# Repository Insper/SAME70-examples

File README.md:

Example projects to the SAME70-XPLD microchip development kit, it is related to the Insper Embedded Computer course:

- https://insper.github.io/ComputacaoEmbarcada/

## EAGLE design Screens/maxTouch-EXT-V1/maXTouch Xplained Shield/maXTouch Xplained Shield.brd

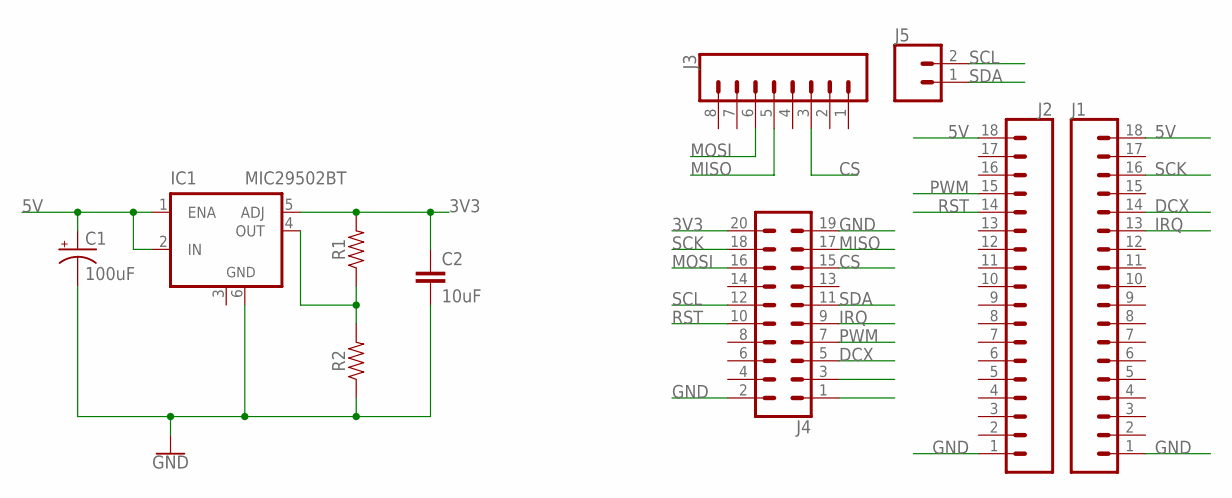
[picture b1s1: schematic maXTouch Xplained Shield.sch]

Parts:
C1: 100uF; PANASONIC_D
C2: 10uF; 0805
IC1: MIC29502BT; TO263-5
J1, J2: CONN_18SILK; 1X18
J3: CONN_08"; 1X08
J4: CONN_10X2; 2X10
J5: CONN_02; 1X02
R1, R2: 0603

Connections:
3V3: C2.1, IC1.5 (ADJ), J4.20, R1.2
5V: C1.+, IC1.1 (ENA), IC1.2 (IN), J1.18, J2.18
CS: J3.3, J4.15
DCX: J1.14, J4.5
GND: C1.-, C2.2, IC1.3 (GND), IC1.6 (GND), J1.1, J2.1, J4.2, J4.19, R2.1
IRQ: J1.13, J4.9
MISO: J3.5, J4.17
MOSI: J3.6, J4.16
unnamed: IC1.4 (OUT), R1.1, R2.2
PWM: J2.15, J4.7
RST: J2.14, J4.10
SCK: J1.16, J4.18
SCL: J4.12, J5.2
SDA: J4.11, J5.1

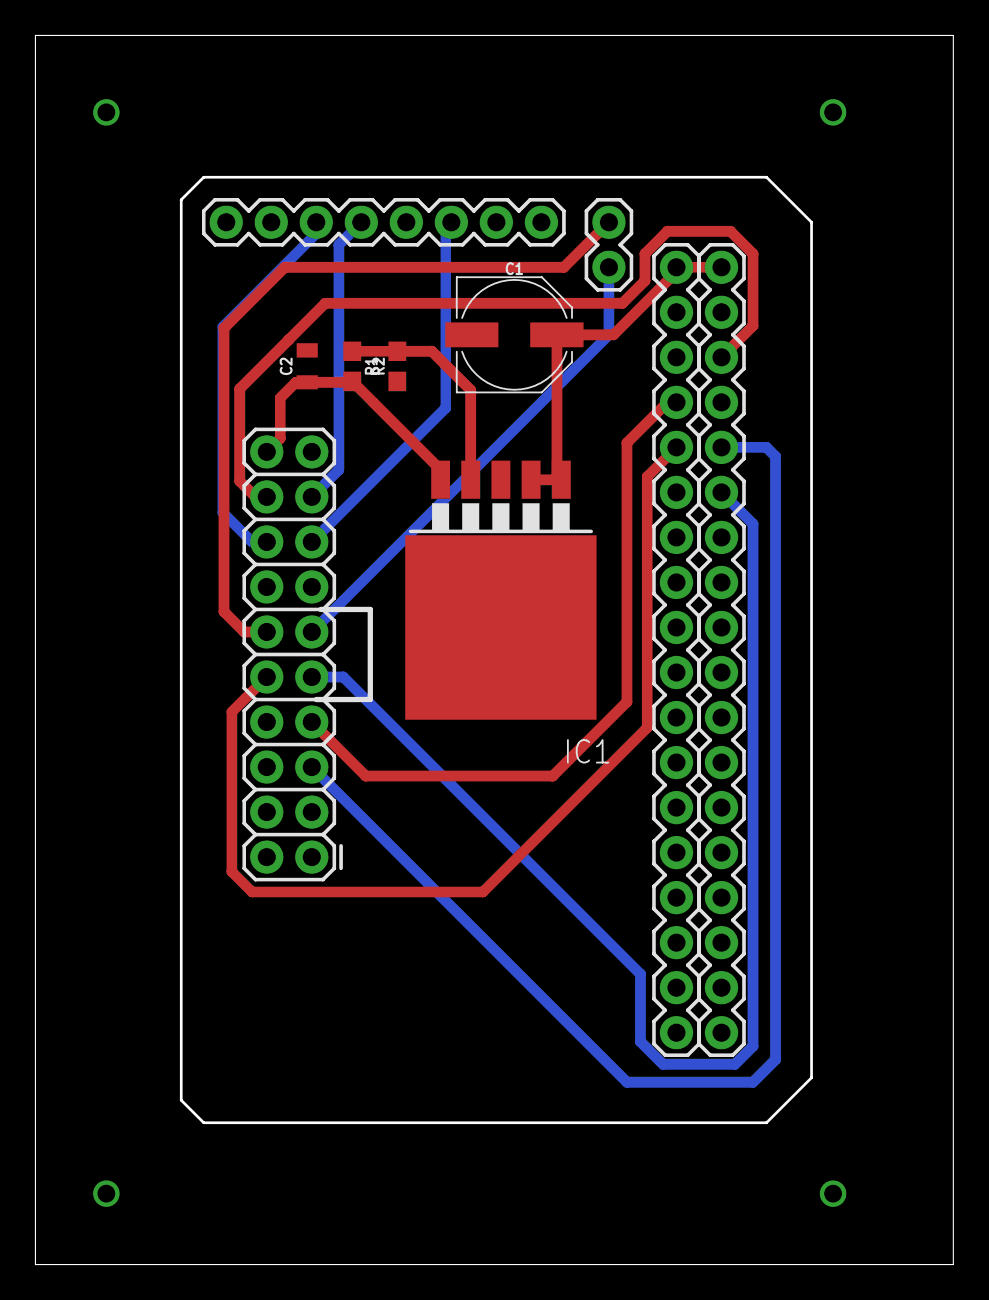
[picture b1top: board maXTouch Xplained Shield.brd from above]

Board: 2 copper layers, 51.6 x 69.2 mm, 10 parts (0 on the bottom side), 14 nets.

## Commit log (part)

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2019-06-06 README OutEXT-LCD-maXTouch
2019-06-06 Nova Imagem
2019-06-06 Nova
2019-06-06 Atualização README
2019-06-06 Atualização REAMDE
2019-06-06 maXTouch Xplained Shield
    Arquivos para prototipação do maXTouch Xplained Shield.
2019-12-09 Pino IRQ Corrigido - PA2 > PA26
2019-12-09 update ethernet
2019-12-09 update bluetooth rtos
2019-12-09 update wifi
2019-12-10 AES AFECs
2019-12-10 periféricos
2019-12-10 maxTouch-EXT-V1
2019-12-10 Removido Arquivos .brd e .sch Antigos
2020-03-02 Update README.md
    Atualizado README
2020-03-02 Update README.md
    README
2020-03-02 Alterado main.c
2020-03-11 Alterados para REV B
2020-03-11 README AFEC-Pin
2020-03-25 oled1 melhorado + novos exemplos
2020-03-30 fix oled1
2020-04-01 Demo RTOS
2020-04-08 afec readme
2020-04-08 update afec pin
2020-04-08 alterado para PC31
2020-04-09 fix screen stack size
2020-04-14 add tc para OLED
2020-04-15 lcd fake para luiza
2020-04-22 debouce touch
2020-04-23 Atualizado README
2020-04-23 subindo imagens doc
2020-05-04 prioridade para 4, pensando no uso em rtos
2020-05-05 Please enter the commit message for your changes. Lines starting exemplo rtos adc
2020-05-12 testando novo formato
2020-05-12 usando fila para comunicar rx e semáforo no IRQ do i2c
2020-05-12 fix clean g_receivedBuffer
2020-05-13 maquina de estados e server com forms
2020-05-13 RTOS-maxTouch-EXT-V1
2020-05-18 Exemplo POST
2020-05-26 correcao
2020-05-26 nova versao do wifi-get
2020-05-27 nova versão wifi
2020-05-27 firmware
2020-06-03 WIFI-WINC1500-post-RTOS-EXT1
2020-06-08 clean
2021-03-01 Alteracao da versao A para a B
2021-03-17 corrigido calculo rtt
2021-03-17 fix calculo rtt
2021-03-20 limpando
2021-03-20 melhorando exemplo proj 1
2021-03-21 melhorando readme
2021-03-22 Rename requeriments.txt to requirements.txt
2021-03-22 firmware demo hc-05
2021-03-22 RTOS-BLUETOOTH
2021-03-25 Substituido led_toggle por pin_toggle
2021-03-30 movendo exemplos lcd maxTouch
2021-04-05 Zsnes
2021-04-05 correção path
2021-04-06 organizando exemplos RTOS
2021-04-06 oled rtos
2021-04-07 Troca do pino PC31 para PD30 do exemplo AFEC-Pin
2021-04-07 alterado exemplo RTOS-OLED para placa B
2021-04-12 montagem lcd adafruit
2021-04-12 melhorando imagens
2021-04-12 image example
2021-04-12 resistive touch example
2021-04-14 2.8-TFT-LCD-ILI9341-image
2021-04-14 2.8-TFT-LCD-ILI9341
2021-04-27 LCD com RTOS
2021-04-27 lcd com lvgl
2021-04-27 exempl oled bluetooth
2021-05-12 Demo do ECG
2021-05-27 Trocado a REV do RTOS-WIFI-get para a versao B
2021-08-04 Issue OLED1 SPI operando em 20M
2021-09-02 fix pio irq
2021-09-27 fix tc freq
2021-10-21 port to lvgl 8
2021-10-25 TRY to fix empty line on lvgl
2021-10-25 add lvg8 files
2022-03-04 Renomeado nome da pasta PRO-SPI
2022-03-09 update example RTT
2022-03-09 melhorias readme rtc
2022-03-09 melhorias main rtc
2022-03-09 Corrigido erros nos exemplos de TC-RTT-RTC
2022-03-09 newoverview
2022-03-21 update demo controle
2022-04-13 lab rtos
2022-04-13 correcoes novos exemplos
2022-05-02 IMU com fusion funcionando
2022-05-02 limpando código
2022-05-02 IMU com fusion funcionando (#7)
    * IMU com fusion funcionando
    * limpando código
2022-05-02 Flex Glove exemplo
2022-05-02 Corrigindo importação errada do fusion
2022-05-28 começando o PIO
2022-05-29 adicionando demo blink-led com Rust
2022-05-29 adicionando delay em assembly
2022-05-31 adicionando APIs para o PIO
2022-06-01 código funcionando
2022-06-01 iniciando o código exemplo
2022-06-04 mudando README
2022-06-04 img onda quadrada
2022-06-04 continuando README
2022-06-04 melhorando o readme
2022-06-04 corrigindo =para ==
2022-06-04 tentando adicionar video
2022-06-05 removendo pasta .vscode
2022-06-05 Ultimas correções
2022-06-05 tirando a pasta debug
2022-06-05 readme e codigo exemplo
2022-06-05 alterando info dos pinos
2022-06-05 inserindo video
2022-06-05 adicionando pasta inicial
2022-06-05 reorganizando pasta
2022-06-06 texto finalizado
2022-06-06 Adiciona Imagem 1
2022-06-06 Finaliza
2022-06-06 Adiciona vídeo
2022-06-06 finalizando codigo comentado
2022-06-07 transformando contador em volatile char
2022-06-08 Arrumando as pastas
2022-06-08 adicionando sugestões
2022-06-08 Comentando o código
2022-06-08 Exemplo Lib C Rand()
2022-06-10 Rust e OpenOCD (#39)
    22a-emb-av3 by https://github.com/Kcpf
2022-06-10 True Random Number Generator - TRNG (#41)
    22a-emb-av3 by https://github.com/BrunoSaboya/SAME70-examples
2022-06-10 Encoder (PIO) (#40)
    22a-emb-av3 by https://github.com/TiagoSeixas2103/SAME70-examples
2022-06-22 Exemplo RTOS-simuladorRODA
2022-07-04 Demo ArqCAR
2022-07-04 Noto Teste Placa
2022-07-04 Novo codigo de TESTE
2022-09-14 update adc to rtos timer
2022-09-15 alterado
2022-09-21 removido incremento rtt
2022-09-27 Update README.md (#45)
    lgtm
2022-10-27 Adiciona demo Fita de LED
2022-11-09 update lab pwm
2022-11-09 update to pd11
2022-11-09 fix figure pd11
2022-11-17 fix stack size on RTOS WINC1500 examples
    Por algum motivo ele não funciona com stack maior que 130.
2022-11-20 Provando minha teoria
2022-12-04 Inicia implementação
2022-12-06 Potenciometro-Motorizado
2022-12-07 corrigindo erros
2022-12-07 Sobe Documentação
2022-12-07 Finaliza documentação e limpeza de código
2022-12-10 Remove pasta debug
2022-12-10 corrigindo readme
2022-12-12 add PCK6 TC
2022-12-12 ATIVA PMC PCK6 TIMER_CLOCK1
2022-12-14 correcao imgs
2022-12-14 Redimensiona imagens
2022-12-14 melhorias
2022-12-14 Potenciômetro Motorizado - ADC/ PWM - biblioteca PID ARM (#48)
    * Potenciometro-Motorizado
2022-12-14 Adiciona links de documentação
2022-12-14 Sobe cabeçalho
2022-12-14 Ajeita descrição de Leads Off
2022-12-14 Ajeita tamanho de gif
2022-12-14 SparkFun Single Lead Heart Rate Monitor - AD8232 (#47)
    * SparkFun Single Lead Heart Rate Monitor
2023-03-27 Atualizando exemplo do RTOS-OLED
2023-03-27 acrescentado pio_get_interrupt_status no codigo
2023-07-25 atualizado programa de teste da placa
2023-07-25 atualizando exemplo
2023-07-25 voltaa
2023-07-25 ultimo recurso
2023-07-26 atualizando teste placa same70
2023-09-14 atualizado nome do exemplo RTOS-AFEC-IRQ

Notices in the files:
parts and their libraries:
SparkFun-Connectors: Licensing: Creative Commons ShareAlike 4.0 International - https://creativecommons.org/licenses/by-sa/4.0
